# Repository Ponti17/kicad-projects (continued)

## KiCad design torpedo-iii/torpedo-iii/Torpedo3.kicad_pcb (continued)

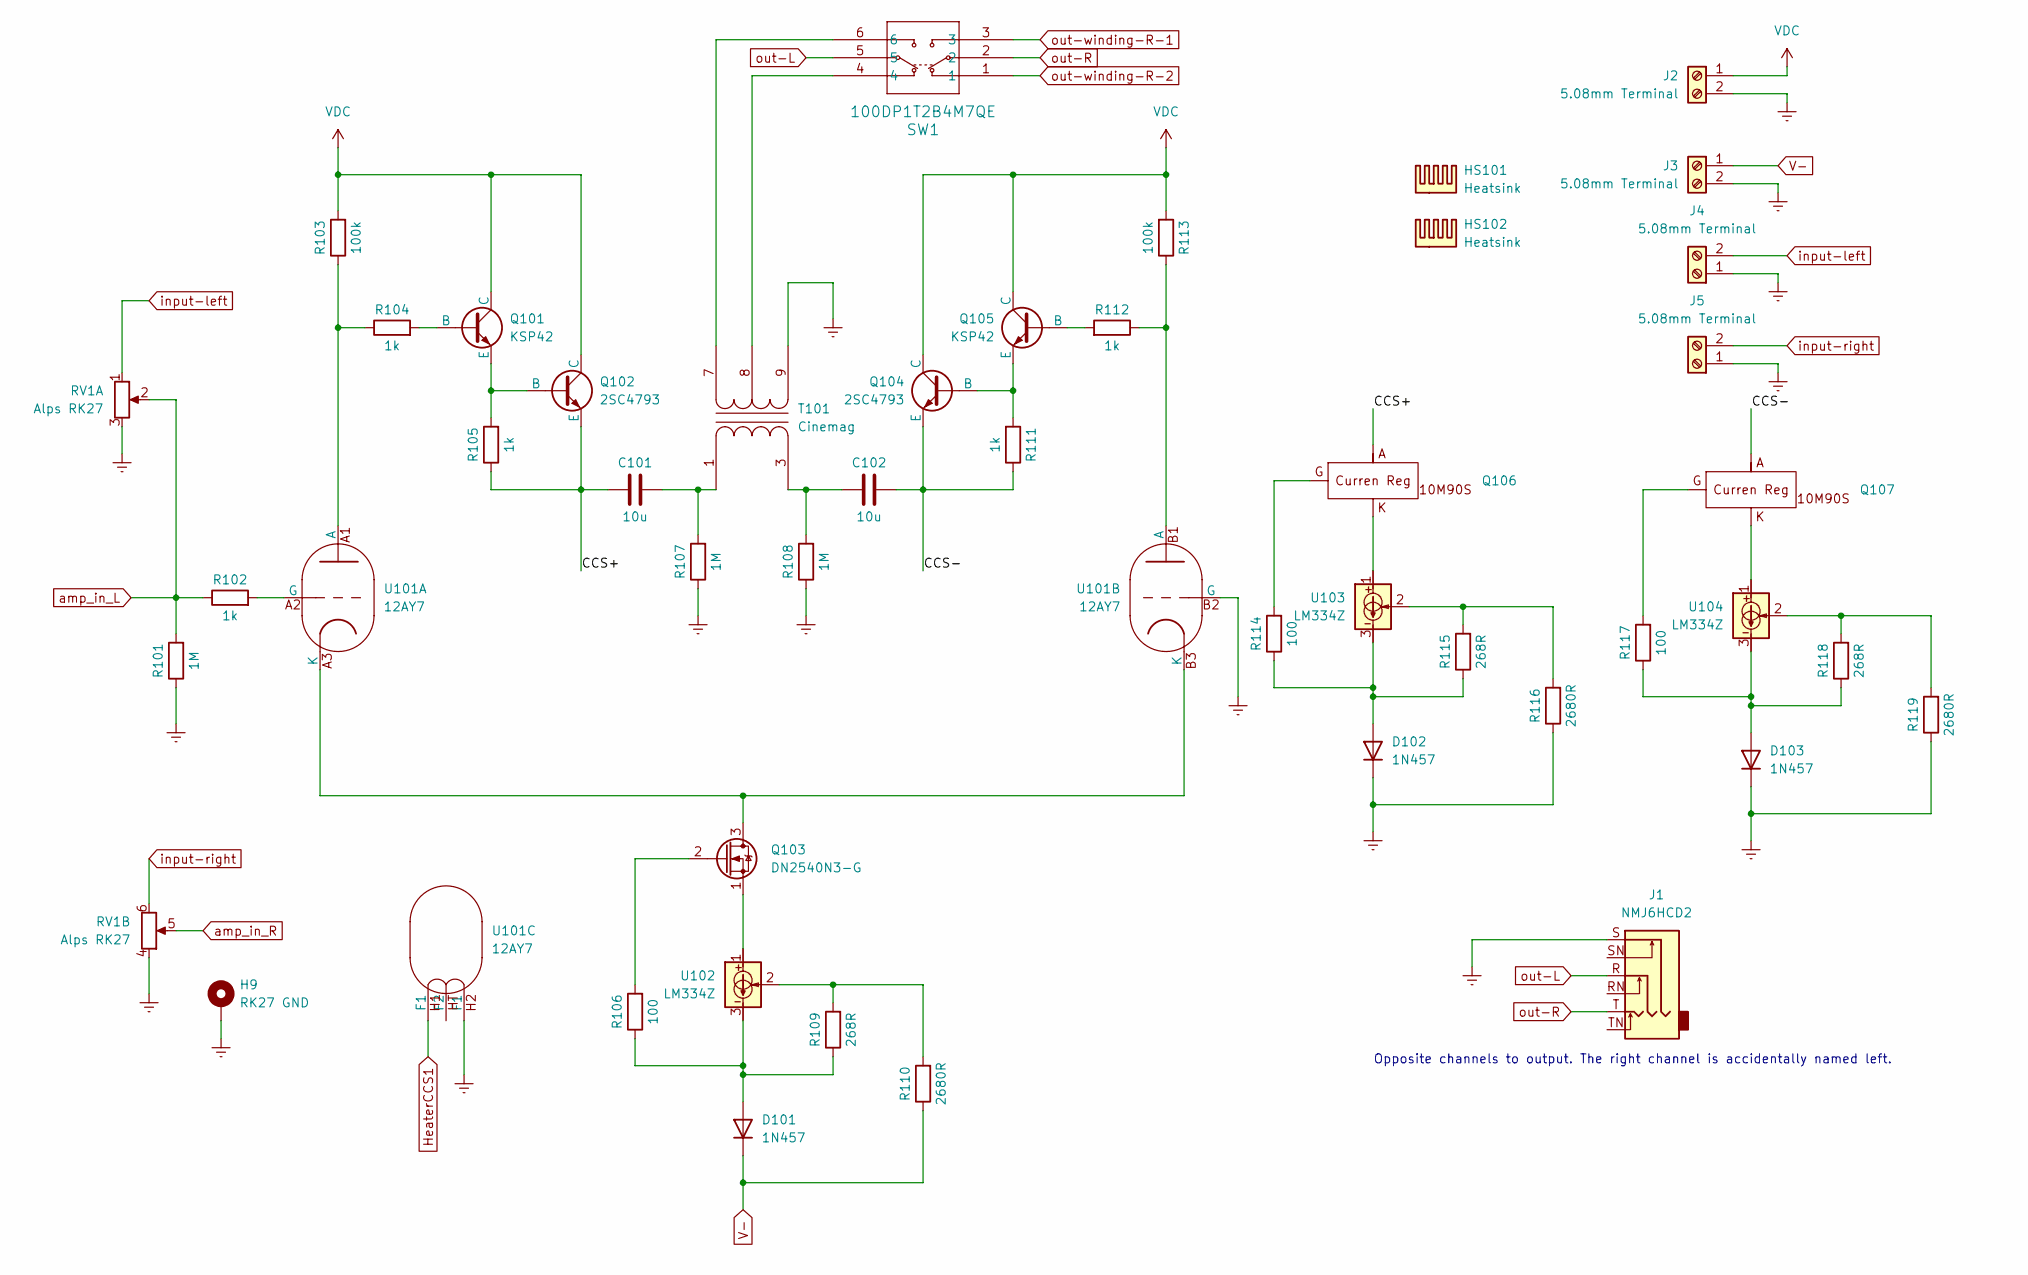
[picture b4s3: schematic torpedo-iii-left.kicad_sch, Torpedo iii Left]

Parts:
C101, C102: 10u; Mundorf Evo 10u
D101, D102, D103: 1N457; D_DO-35_SOD27_P7.62mm_Horizontal
H9: RK27 GND; MountingHole_2.5mm_Pad
HS101, HS102: Heatsink; 513102B02500G
J1: NMJ6HCD2; Jack_6.35mm_Neutrik_NMJ6HCD2_Horizontal
J2, J3, J4, J5: 5.08mm Terminal; TerminalBlock_Phoenix_MKDS-1,5-2-5.08_1x02_P5.08mm_Horizont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
Q101, Q105: KSP42; TO-92_Inline_Wide
Q102, Q104: 2SC4793; TO-220-3_Vertical
Q103: DN2540N3-G; TO-92_Inline_Wide
Q106, Q107: TO-220-3_Vertical
R101, R107, R108: 1M; R_Axial_DIN0309_L9.0mm_D3.2mm_P12.70mm_Horizontal
R102, R104, R105, R111, R112: 1k; R_Axial_DIN0309_L9.0mm_D3.2mm_P12.70mm_Horizontal
R103, R113: 100k; R_Axial_DIN0414_L11.9mm_D4.5mm_P15.24mm_Horizontal
R106, R114, R117: 100; R_Axial_DIN0309_L9.0mm_D3.2mm_P12.70mm_Horizontal
R109, R115, R118: 268R; R_Axial_DIN0309_L9.0mm_D3.2mm_P12.70mm_Horizontal
R110, R116, R119: 2680R; R_Axial_DIN0309_L9.0mm_D3.2mm_P12.70mm_Horizontal
RV1: Alps RK27; Alps RK27 Stereo
SW1: 100DP1T2B4M7QE; 100DP1T2B4M7QE_EWI
T101: Cinemag; Cinemag CM-15615PC
U101: 12AY7
U102, U103, U104: LM334Z; TO-92_Inline_Wide

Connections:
/Torpedo-iii-left/CCS+: C101.1, Q102.3 (E), Q106.2, R105.1
/Torpedo-iii-left/CCS-: C102.1, Q104.3 (E), Q107.2, R111.1
GNDREF: D102.1 (K), D103.1 (K), H9.1, J1.S, J2.2, J3.2, J4.1, J5.1, R101.1, R107.1, R108.1, R116.1, R119.1, RV1.3, RV1.4, T101.9 (SA), U101.B2 (G), U101.H2 (F1); also elsewhere on the board
HeaterCCS1: U101.H1 (F1); also elsewhere on the board
unnamed: D101.2 (A), R106.1, R109.1, U102.3
unnamed: D102.2 (A), R114.1, R115.1, U103.3
unnamed: D103.2 (A), R117.1, R118.1, U104.3
unnamed: Q101.2 (B), R104.2
unnamed: Q101.1 (E), Q102.1 (B), R105.2
unnamed: Q103.3 (D), U101.A3 (K), U101.B3 (K)
unnamed: Q103.2 (G), R106.2
unnamed: Q103.1 (S), U102.1
unnamed: Q104.1 (B), Q105.1 (E), R111.2
unnamed: Q105.2 (B), R112.2
unnamed: Q106.1, R114.2
unnamed: Q106.3, U103.1
unnamed: Q107.1, R117.2
unnamed: Q107.3, U104.1
unnamed: R109.2, R110.2, U102.2
unnamed: R115.2, R116.2, U103.2
unnamed: R118.2, R119.2, U104.2
unnamed: C101.2, R107.2, T101.1 (AA)
unnamed: C102.2, R108.2, T101.3 (AB)
unnamed: SW1.6, T101.7 (SB)
unnamed: SW1.4, T101.8 (SC)
unnamed: R103.1, R104.1, U101.A1 (A)
unnamed: R102.2, U101.A2 (G)
unnamed: R112.1, R113.1, U101.B1 (A)
V-: D101.1 (K), J3.1, R110.1; also elsewhere on the board
VDC: J2.1, Q101.3 (C), Q102.2 (C), Q104.2 (C), Q105.3 (C), R103.2, R113.2; also elsewhere on the board
amp_in_L: R101.2, R102.1, RV1.2
amp_in_R: RV1.5; also elsewhere on the board
input-left: J4.2, RV1.1
input-right: J5.2, RV1.6
out-L: J1.R, SW1.5
out-R: J1.T, SW1.2
out-winding-R-1: SW1.3; also elsewhere on the board
out-winding-R-2: SW1.1; also elsewhere on the board

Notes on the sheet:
Opposite channels to output. The right channel is accidentally named left.

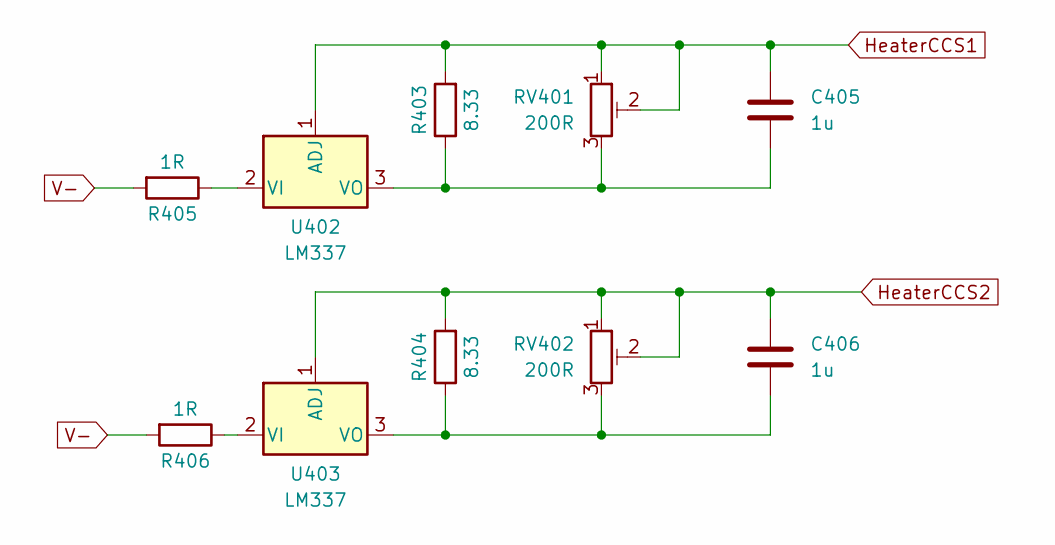
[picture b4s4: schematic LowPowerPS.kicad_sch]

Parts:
C405, C406: 1u; C_Disc_D7.5mm_W2.5mm_P5.00mm
R403, R404: 8.33; R_Axial_DIN0309_L9.0mm_D3.2mm_P12.70mm_Horizontal
R405, R406: 1R; R_Axial_DIN0309_L9.0mm_D3.2mm_P12.70mm_Horizontal
RV401, RV402: 200R; Potentiometer_Bourns_3296W_Vertical
U402, U403: LM337; TO-220-3_Vertical

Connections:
HeaterCCS1: C405.1, R403.2, RV401.1, RV401.2, U402.1 (ADJ); also elsewhere on the board
HeaterCCS2: C406.1, R404.2, RV402.1, RV402.2, U403.1 (ADJ); also elsewhere on the board
unnamed: R405.1, U402.2 (VI)
unnamed: C405.2, R403.1, RV401.3, U402.3 (VO)
unnamed: R406.1, U403.2 (VI)
unnamed: C406.2, R404.1, RV402.3, U403.3 (VO)
V-: R405.2, R406.2; also elsewhere on the board

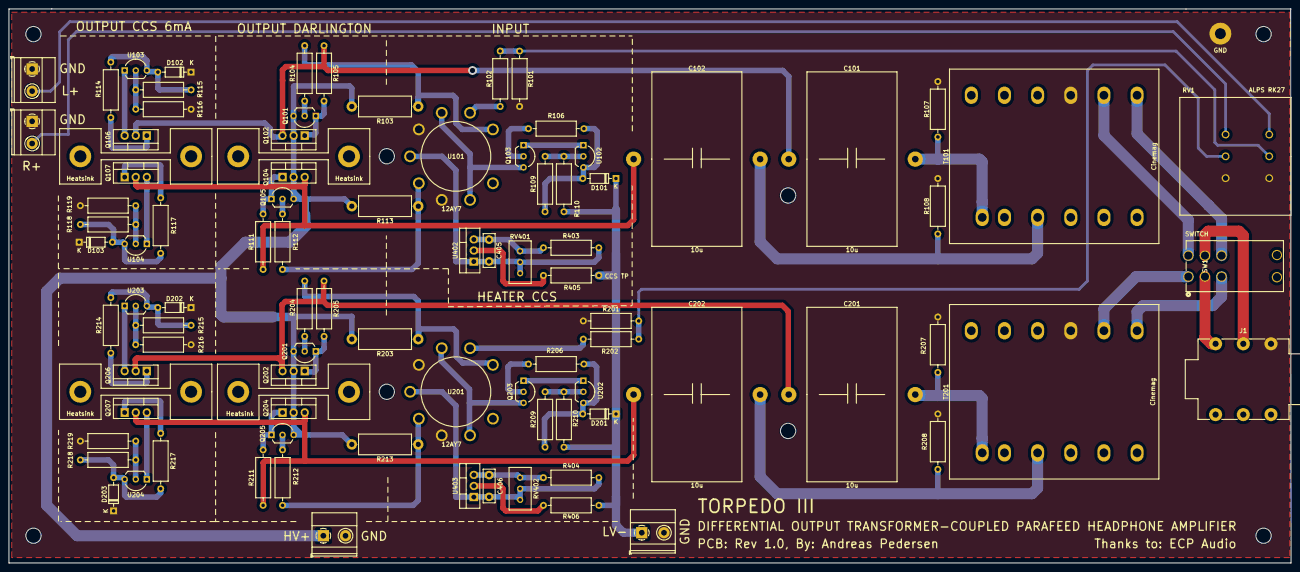
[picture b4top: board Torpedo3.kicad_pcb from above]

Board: 2 copper layers, 293.9 x 127.0 mm, 102 parts (0 on the bottom side), 67 nets.

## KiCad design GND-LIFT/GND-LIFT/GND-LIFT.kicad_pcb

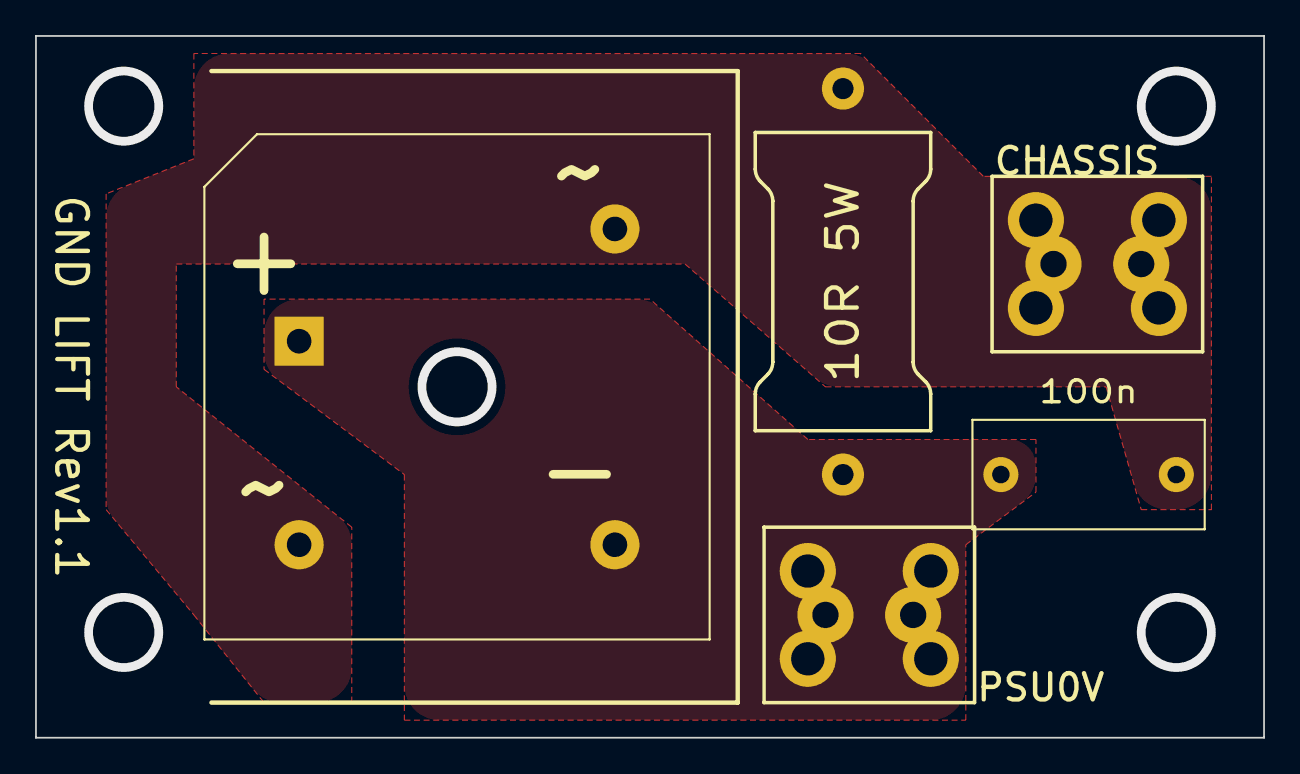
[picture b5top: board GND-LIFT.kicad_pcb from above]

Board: 2 copper layers, 70.0 x 40.0 mm, 5 parts (0 on the bottom side), 2 nets, no tracks yet.

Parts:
C1: 100n; C_Rect_L13.0mm_W6.0mm_P10.00mm_FKS3_FKP3_MKS4
D1: D_Bridge_+A-A; Diode_Bridge_28.6x28.6x7.3mm_P18.0mm_P11.6mm
J1, J2: 8191; KEYSTONE_8191
R1: 10R 5W; VishayAC05

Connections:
/CHASSIS: C1.2, D1.2, D1.4, J2.1, R1.2
/PSU0V: C1.1, D1.1 (+), D1.3 (-), J1.1, R1.1

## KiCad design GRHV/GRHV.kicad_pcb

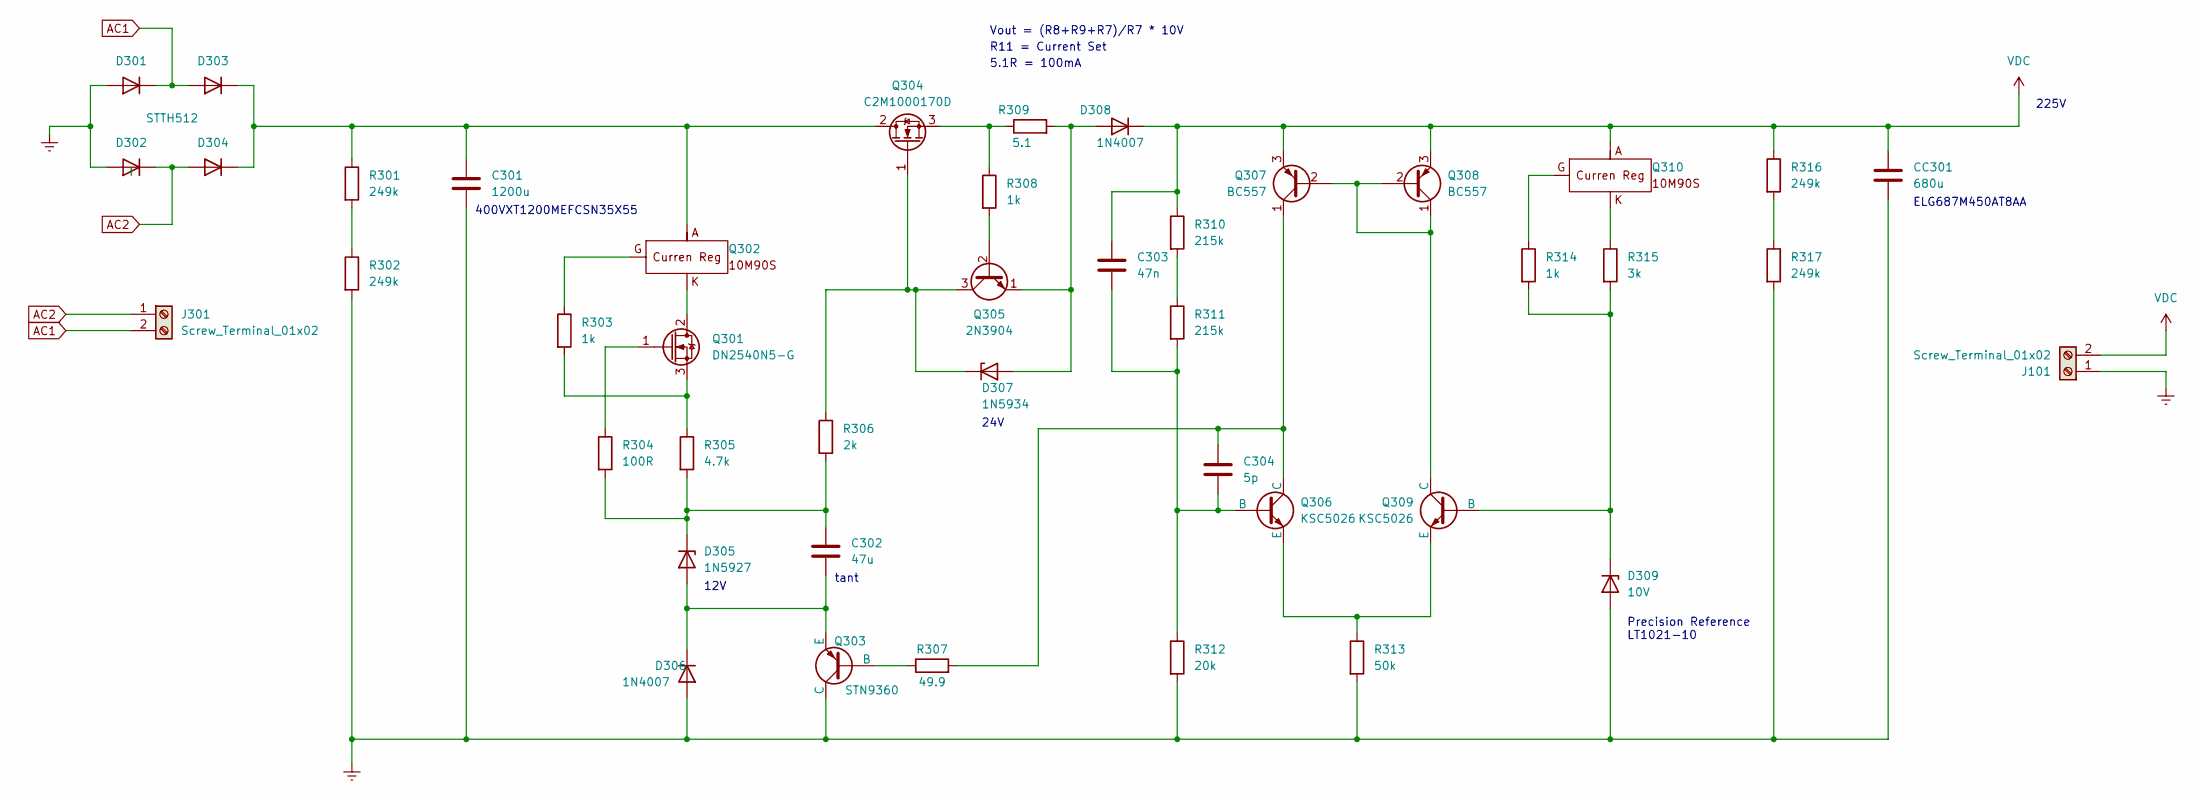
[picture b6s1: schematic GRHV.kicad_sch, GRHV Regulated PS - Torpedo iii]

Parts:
C301: 1200u; CP_Radial_D35.0mm_P10.00mm_SnapIn
C302: 47u; CP_Radial_Tantal_D9.0mm_P5.00mm
C303: 47n; C_Rect_L18.0mm_W8.0mm_P15.00mm_FKS3_FKP3
C304: 5p; C_Disc_D7.5mm_W2.5mm_P5.00mm
CC301: 680u; CP_Radial_D35.0mm_P10.00mm_SnapIn
D301, D302, D303, D304: STTH512; TO-220-2_Vertical
D305: 1N5927; D_DO-41_SOD81_P10.16mm_Horizontal
D306, D308: 1N4007; D_DO-41_SOD81_P10.16mm_Horizontal
D307: 1N5934; D_DO-41_SOD81_P10.16mm_Horizontal
D309: 10V; LT1021
J101, J301: Screw_Terminal_01x02; TerminalBlock_Phoenix_MKDS-1,5-2-5.08_1x02_P5.08mm_Horizont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
Q301: DN2540N5-G; TO-220-3_Vertical
Q302, Q310: TO-220-3_Vertical
Q303: STN9360
Q304: C2M1000170D; TO-247-3_Vertical
Q305: 2N3904; TO-92_Inline_Wide
Q306, Q309: KSC5026
Q307, Q308: BC557; TO-92_Inline_Wide
R301, R302, R316, R317: 249k; R_Axial_DIN0309_L9.0mm_D3.2mm_P12.70mm_Horizontal
R303, R308, R314: 1k; R_Axial_DIN0309_L9.0mm_D3.2mm_P12.70mm_Horizontal
R304: 100R; R_Axial_DIN0309_L9.0mm_D3.2mm_P12.70mm_Horizontal
R305: 4.7k; R_Axial_DIN0309_L9.0mm_D3.2mm_P12.70mm_Horizontal
R306: 2k; R_Axial_DIN0309_L9.0mm_D3.2mm_P12.70mm_Horizontal
R307: 49.9; R_Axial_DIN0309_L9.0mm_D3.2mm_P12.70mm_Horizontal
R309: 5.1; R_Axial_DIN0516_L15.5mm_D5.0mm_P25.40mm_Horizontal
R310, R311: 215k; R_Axial_DIN0309_L9.0mm_D3.2mm_P12.70mm_Horizontal
R312: 20k; R_Axial_DIN0309_L9.0mm_D3.2mm_P12.70mm_Horizontal
R313: 50k; R_Axial_DIN0309_L9.0mm_D3.2mm_P12.70mm_Horizontal
R315: 3k; R_Axial_DIN0309_L9.0mm_D3.2mm_P12.70mm_Horizontal

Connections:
AC1: D301.1 (K), D303.2 (A), J301.2
AC2: D302.1 (K), D304.2 (A), J301.1
GNDREF: C301.2, CC301.2, D301.2 (A), D302.2 (A), D306.2 (A), D309.2 (A), J101.1, Q303.1 (C), R302.2, R312.2, R313.2, R317.2
unnamed: C301.1, D303.1 (K), D304.1 (K), Q302.2, Q304.2 (D), R301.1
unnamed: C302.2, D305.2 (A), D306.1 (K), Q303.3 (E)
unnamed: C302.1, D305.1 (K), R304.2, R305.2, R306.2
unnamed: D307.2 (A), D308.2 (A), Q305.1 (E), R309.2
unnamed: D307.1 (K), Q304.1 (G), Q305.3 (C), R306.1
unnamed: D309.1 (K), Q309.2 (B), R314.2, R315.2
unnamed: Q301.2 (D), Q302.3
unnamed: Q301.1 (G), R304.1
unnamed: Q301.3 (S), R303.2, R305.1
unnamed: Q302.1, R303.1
unnamed: Q303.2 (B), R307.1
unnamed: Q304.3 (S), R308.1, R309.1
unnamed: Q305.2 (B), R308.2
unnamed: C303.2, C304.2, Q306.2 (B), R311.2, R312.1
unnamed: C304.1, Q306.1 (C), Q307.1 (C), R307.2
unnamed: Q306.3 (E), Q309.3 (E), R313.1
unnamed: Q307.2 (B), Q308.1 (C), Q308.2 (B), Q309.1 (C)
unnamed: Q310.1, R314.1
unnamed: Q310.3, R315.1
unnamed: R301.2, R302.1
unnamed: R310.2, R311.1
unnamed: R316.2, R317.1
VDC: C303.1, CC301.1, D308.1 (K), J101.2, Q307.3 (E), Q308.3 (E), Q310.2, R310.1, R316.1

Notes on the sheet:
12V
5.1R = 100mA
24V
Precision Reference LT1021-10
tant
Vout = (R8+R9+R7)/R7 * 10V
400VXT1200MEFCSN35X55
ELG687M450AT8AA
R11 = Current Set
225V

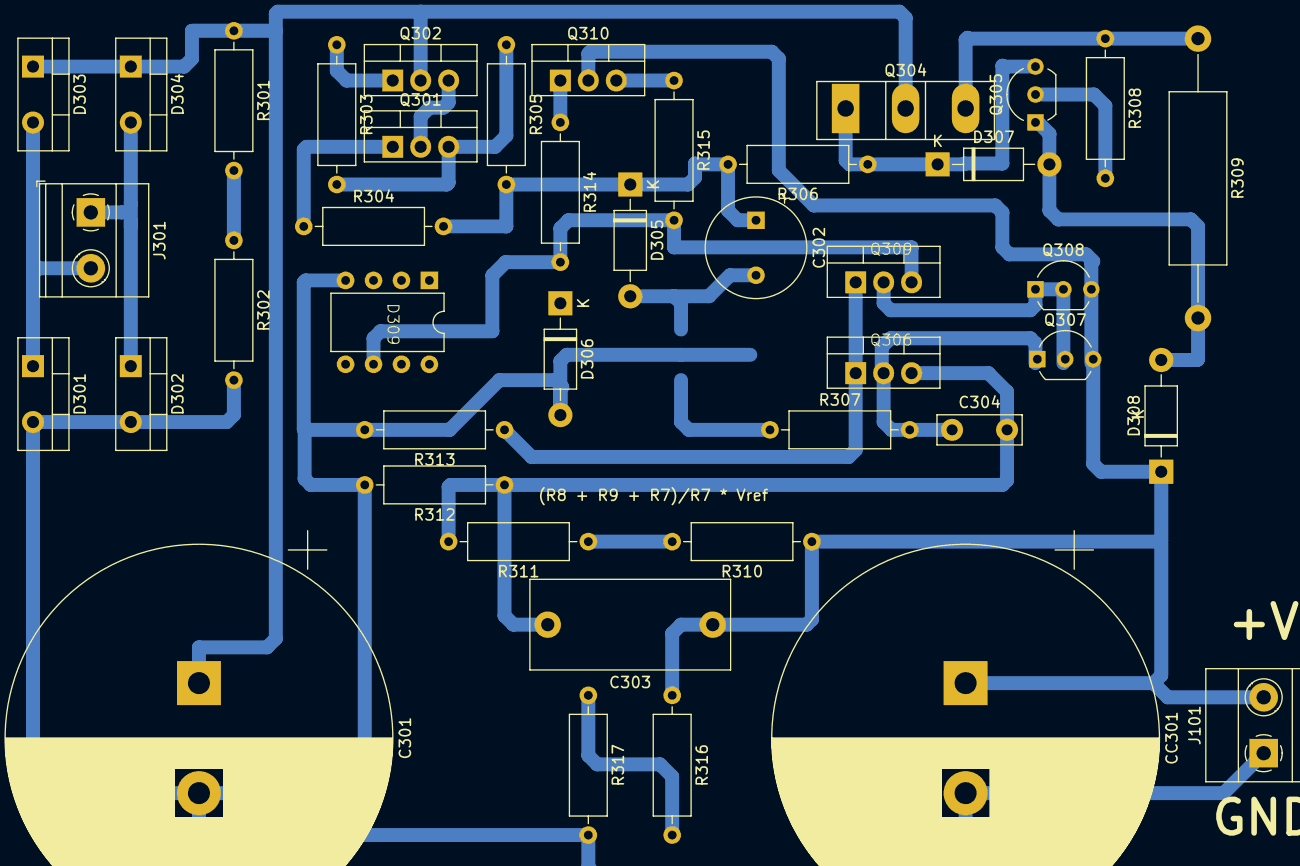
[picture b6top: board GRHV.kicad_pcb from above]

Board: 2 copper layers, 43 parts (1 on the bottom side), 26 nets.

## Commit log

2024-03-07 gnd-lift rev1.1
    fix silkscreen
2024-03-07 fix gnd-lift - add gerbers for gnd-lift & t-gnd
2024-06-14 update t-gnd
2024-06-14 add cfa3-controller
2024-06-14 update torpedo-iii
2024-06-14 add wolverine-protection
2024-06-14 update gitignore
2024-07-14 add GND lift
2024-07-14 add GRHV
    Golden Reference High Voltage
2024-07-14 add LED controller
2024-07-14 add T-GND
2024-07-14 add torpedo-iii
2024-07-14 add .gitignore
2024-07-14 add cfa3 controller
2024-07-17 update wolverine 16-07-24
2024-07-17 add wolverine
2024-07-17 ignore fabrication outputs
